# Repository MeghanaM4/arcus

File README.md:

# arcus
Hack Club's Parthenon PCB Badge (with an RP2040 and ePaper display)

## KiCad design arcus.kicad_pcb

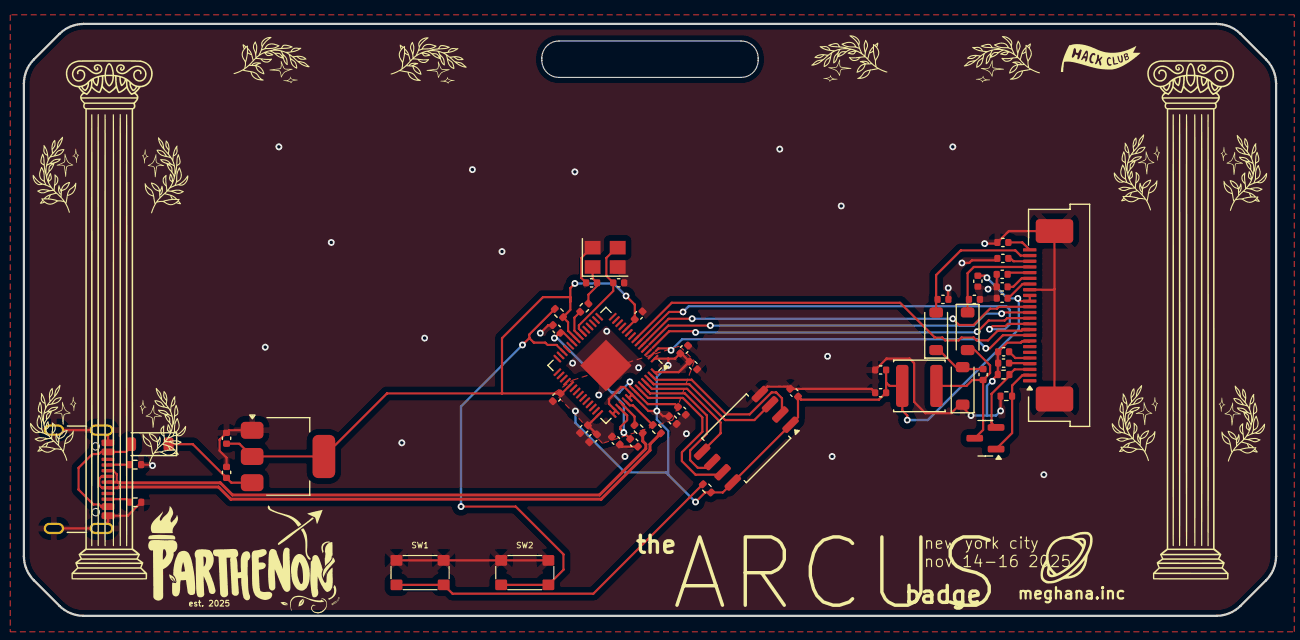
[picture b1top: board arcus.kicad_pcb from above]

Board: 2 copper layers, 110.0 x 52.0 mm, 52 parts (0 on the bottom side), 40 nets.

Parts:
C1, C2, C3, C4, C5, C7, C8, C9, C10, C13, C21, C28: 1μF; C_0402_1005Metric
C6, C14, C15, C16, C17, C18, C19, C20, C22, C23, C24: 100nF; C_0402_1005Metric
C11, C12: 10μF; C_0402_1005Metric
C25, C26: 15pF; C_0402_1005Metric
C27, C29: 4.7μF; C_0402_1005Metric
D1, D5, D6, D7: MBR0530; D_SOD-123
J2: USB_C_Receptacle_USB2.0_16P; USB_C_Receptacle_GCT_USB4105-xx-A_16P_TopMnt_Horizontal
L2: 10μH 1A; L_APV_ANR4018
Q3: IRLML2060; SOT-23
R1, R2: 27.4Ω; R_0402_1005Metric
R3, R4: 5.1kΩ; R_0402_1005Metric
R5, R6: 1kΩ; R_0402_1005Metric
R7, R10: 10kΩ; R_0402_1005Metric
R11: 0.47Ω; R_0402_1005Metric
SW1: SW_PUSH; SW_Push_SPST_TSA016
SW2: SW_Push; SW_Push_SPST_TSA016
U1: AFC07-S24FCA-00; LCSC_1x24-1MP_P0.5mm_Horizontal
U2: RP2040; QFN-56-1EP_7x7mm_P0.4mm_EP3.2x3.2mm
U3: AMS1117-3.3; SOT-223-3_TabPin2
U4: W25Q128JVSIQ; SOIC-8_5.3x5.3mm_P1.27mm
Y1: ABM8-272-T3; Crystal_SMD_Abracon_ABM8G-4Pin_3.2x2.5mm

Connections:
+1V1: C21.1, C22.1, C23.1, U2.23 (DVDD), U2.45 (VREG_VOUT), U2.50 (DVDD)
+3V3: C6.2, C7.2, C11.1, C13.1, C14.1, C15.1, C16.1, C17.1, C18.1, C19.1, C20.1, C24.1, C29.1, L2.1, R5.2, R7.1, U1.15 (VDDIO), U1.16 (VCI), U2.1 (IOVDD), U2.10 (IOVDD), U2.22 (IOVDD), U2.33 (IOVDD), U2.42 (IOVDD), U2.43 (ADC_AVDD), U2.44 (VREG_IN), U2.48 (USB_VDD), U2.49 (IOVDD), U2.56 (QSPI_SS), U3.2 (VO), U4.1 (~CS), U4.8 (VCC)
+5V: C12.1, D1.1 (K), U3.3 (VI)
/BUSY: U1.9 (BUSY), U2.2 (GPIO0)
/CLK: U1.13 (SCL), U2.4 (GPIO2)
/CS: U1.12 (~CS), U2.3 (GPIO1)
/D/C: U1.11 (~D/C), U2.6 (GPIO4)
/GDR: Q3.1 (G), R10.1, U1.2 (GDR)
/MOSI: U1.14 (SDA), U2.5 (GPIO3)
/QSPI_CLK: U2.52 (QSPI_SCLK), U4.6 (CLK)
/QSPI_SD0: U2.53 (QSPI_SD0), U4.5 (DI/IO_{0})
/QSPI_SD1: U2.55 (QSPI_SD1), U4.2 (DO/IO_{1})
/QSPI_SD2: U2.54 (QSPI_SD2), U4.3 (~WP/IO_{2})
/QSPI_SD3: U2.51 (QSPI_SD3), U4.7 (~HOLD/~RESET/IO_{3})
/RESE: Q3.2 (S), R11.1, U1.3 (RESE)
/RST: U1.10 (~RST), U2.7 (GPIO5)
/USB_D+: J2.A6 (D+), J2.B6 (D+), R1.1
/USB_D-: J2.A7 (D-), J2.B7 (D-), R2.1
/VGH: C3.2, D7.1 (K), U1.21 (VGH)
/VGL: C10.2, D5.2 (A), U1.23 (VGL)
/XIN: C25.2, U2.20 (XIN), Y1.3
/XOUT: R6.2, U2.21 (XOUT)
GND: C1.1, C2.1, C3.1, C4.1, C5.1, C6.1, C7.1, C8.1, C9.1, C10.1, C11.2, C12.2, C13.2, C14.2, C15.2, C16.2, C17.2, C18.2, C19.2, C20.2, C21.2, C22.2, C23.2, C24.2, C25.1, C26.1, C28.1, C29.2, D6.1 (K), J2.A1 (GND), J2.A12 (GND), J2.B1 (GND), J2.B12 (GND), J2.S1 (SHIELD), R3.2, R4.2, R10.2, R11.2, SW1.1, SW2.1, U1.8 (BS1), U1.17 (VSS), U1.MP (SHIELD), U2.57 (GND), U3.1 (GND), U4.4 (GND), Y1.2, Y1.4
unnamed: C26.2, R6.1, Y1.1
unnamed: D1.2 (A), J2.A4 (VBUS), J2.A9 (VBUS), J2.B4 (VBUS), J2.B9 (VBUS)
unnamed: C27.1, D5.1 (K), D6.2 (A)
unnamed: C27.2, D7.2 (A), L2.2, Q3.3 (D)
unnamed: J2.A5 (CC1), R3.1
unnamed: J2.B5 (CC2), R4.1
unnamed: R5.1, SW1.2
unnamed: C1.2, U1.24 (VCOM)
unnamed: C5.2, U1.18 (VDD)
unnamed: C8.2, U1.4 (VGL/NC)
unnamed: C28.2, U1.19 (VPP)
unnamed: C4.2, U1.20 (VSH1)
unnamed: C9.2, U1.5 (VSH2)
unnamed: C2.2, U1.22 (VSL)
unnamed: R7.2, SW2.2, U2.26 (RUN)
unnamed: R2.2, U2.46 (USB_DM)
unnamed: R1.2, U2.47 (USB_DP)

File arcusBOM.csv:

Designator,Designator,Footprint,JLCPCB Part #
"D1,D7,D5,D6",MBR0530,D_SOD-123F,C5204746
J2,USB_C_Receptacle_USB2.0_16P,USB_C_Receptacle_GCT_USB4105-xx-A_16P_TopMnt_Horizontal,C2765186
Y1,ABM8-272-T3,Crystal_SMD_Abracon_ABM8G-4Pin_3.2x2.5mm,C20625731
"C10,C8,C28,C13,C1,C3,C4,C21,C7,C9,C5,C2",1μF,C_0402_1005Metric,C14445
"C20,C22,C6,C17,C16,C18,C19,C15,C23,C24,C14",100nF,C_0402_1005Metric,C1525
"C26,C25",15pF,C_0402_1005Metric,C1548
"R1,R2",27.4Ω,R_0402_1005Metric,C31439
R11,0.47Ω,R_0402_1005Metric,C423102
L2,10μH 1A,L_APV_ANR4018,C6808084
SW1,SW_PUSH,SW_Push_SPST_TSA016,C2888430
"C27,C29",4.7μF,C_0402_1005Metric,C23687
SW2,SW_Push,SW_Push_SPST_TSA016,C2888430
U3,AMS1117-3.3,SOT-223-3_TabPin2,C347222
"R7,R10",10kΩ,R_0402_1005Metric,C25531
U4,W25Q128JVSIQ,SOIC-8_5.3x5.3mm_P1.27mm,C97521
"R6,R5",1kΩ,R_0402_1005Metric,C11702
Q3,IRLML2060,SOT-23,C5122027
"C11,C12",10μF,C_0402_1005Metric,C15525
"R3,R4",5.1kΩ,R_0402_1005Metric,C25905
U1,AFC07-S24FCA-00,LCSC_1x24-1MP_P0.5mm_Horizontal,C262567
U2,RP2040,QFN-56-1EP_7x7mm_P0.4mm_EP3.2x3.2mm,C2040

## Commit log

2025-11-19 add files
2025-12-05 Add images to README
